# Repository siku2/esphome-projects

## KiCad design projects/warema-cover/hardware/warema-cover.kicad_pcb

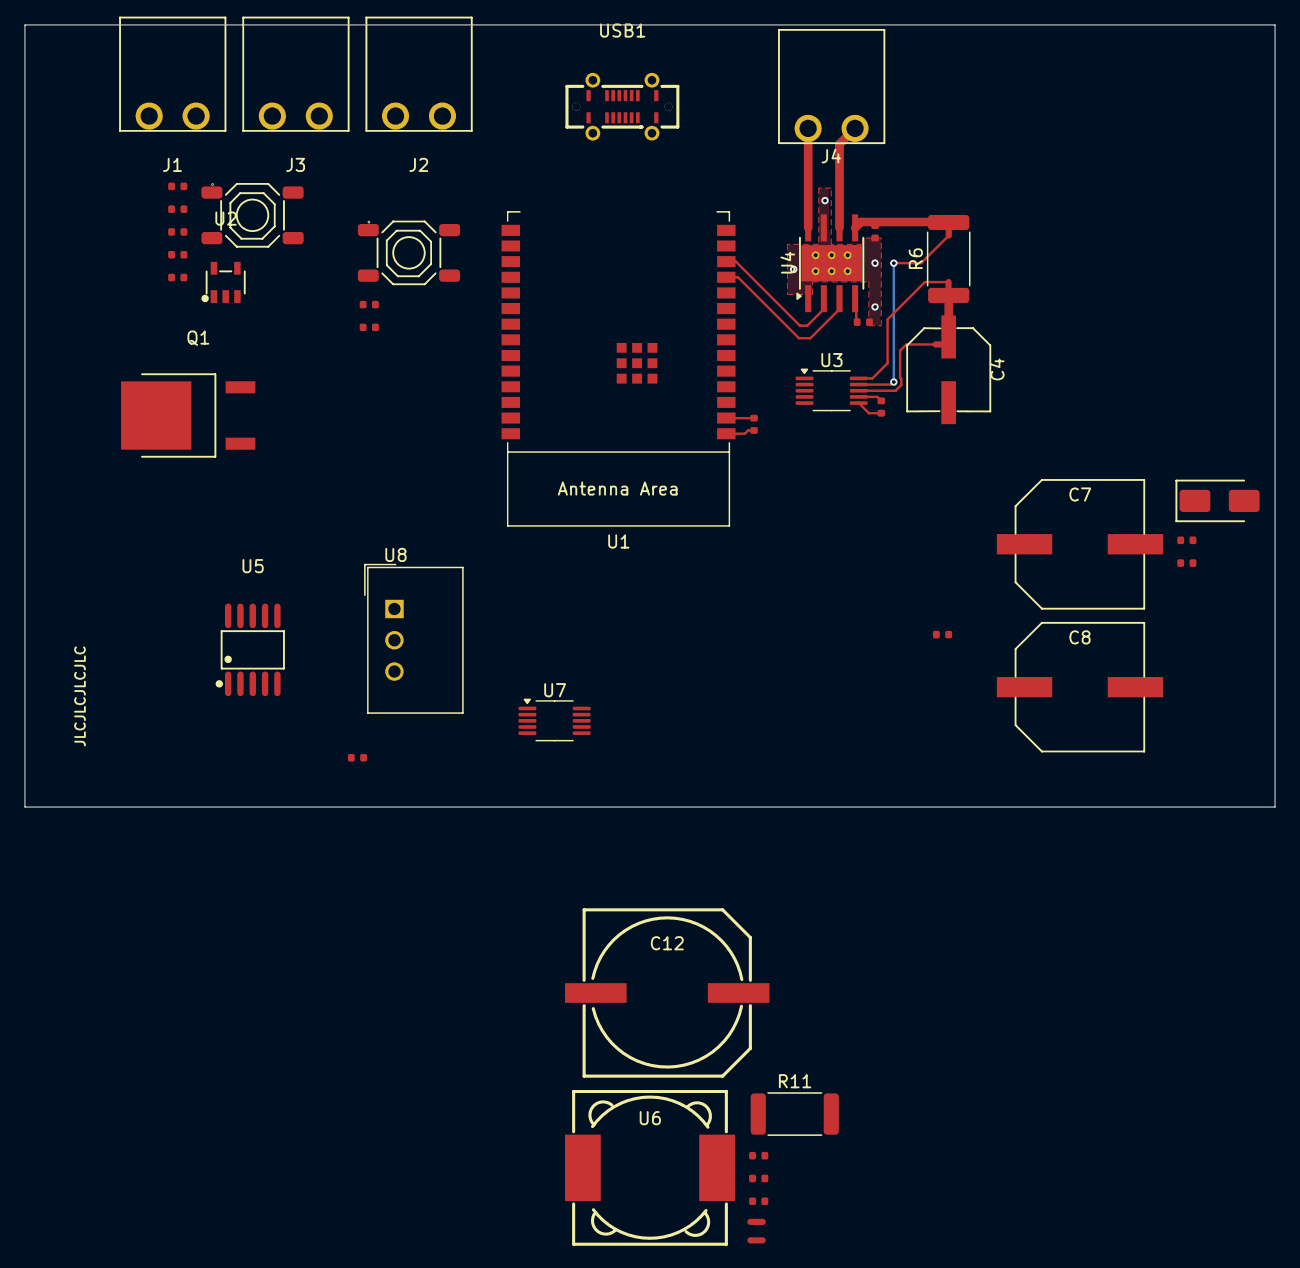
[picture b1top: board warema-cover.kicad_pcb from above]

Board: 2 copper layers, 101.5 x 63.5 mm, 47 parts (0 on the bottom side), 33 nets.

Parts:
C1, C2, C3, C5, C6, C9, C11, C13: 100nF; C_0402
C4: 47uF; CAP-SMD_BD6.3-L6.6-W6.6-LS7.6-FD
C7, C8: 470uF; CAP-SMD_BD10.0-L10.3-W10.3-LS11.0-FD
C10: 220nF; C_0402
C12: 1000uF; CAP-SMD_BD12.5-L13.0-W13.0-RD
D1: SS54; D_SMA
J1: Power Supply; CONN-TH_2P-P3.81_MAX_MX15EDGR-3.81-GN01-02P-CU-A
J2: Solar Panel; CONN-TH_2P-P3.81_MAX_MX15EDGR-3.81-GN01-02P-CU-A
J3: Battery; CONN-TH_2P-P3.81_MAX_MX15EDGR-3.81-GN01-02P-CU-A
J4: Motor; CONN-TH_2P-P3.81_MAX_MX15EDGR-3.81-GN01-02P-CU-A
NT1, NT2, NT3, NT4, NT5: NetTie_2; NetTie-2_SMD_Pad0.5mm
PN1: Part_Num_JLCPCB
Q1: AOD4185_C879147; TO-252-2_L6.6-W6.1-P4.58-LS9.9-BR
R1, R2, R4: 100kΩ; R_0402
R3, R5: 5.1kΩ; R_0402
R6: 15mΩ; R_2512_6332Metric
R7: 24kΩ; R_0402
R8: 120Ω; R_0402
R9: 220kΩ; R_0402
R10: 15kΩ; R_0402
R11: 30mΩ; R_2512_6332Metric
S1, S2: Tactile Button, 160gf; SW-SMD_4P-L5.1-W5.1-P3.70-LS6.5-TL-2
U1: ESP32-C6-WROOM-1
U2: RT9080-33GJ5; TSOT-23-5_L2.9-W1.6-P0.95-LS2.8-BL
U3, U7: INA228; VSSOP-10_3x3mm_P0.5mm
U4: DRV8871DDA; Texas_HTSOP-8-1EP_3.9x4.9mm_P1.27mm_EP2.95x4.9mm_Mask2.4x3.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
U5: CN3767; SSOP-10_L4.9-W3.9-P1.00-LS6.0-BL
U6: CYH125-47UH; IND-SMD_L12.3-W12.3
U8: TSR1-2433E; Converter_DCDC_TRACO_TSR1-xxxxE_THT
USB1: GT-USB-7055BB; USB-C-TH_GT-USB-7055BB

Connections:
+3.3V: C3.2, C5.1, C13.1, R1.1, R2.2, U1.2 (3V3), U2.5 (VOUT), U3.6 (VS), U7.2 (A0), U7.6 (VS), U8.3 (Vout)
+12V: C4.1, C11.2, C12.1, J3.1, NT1.1, NT2.1, NT5.1, R6.1, R11.2, U8.1 (Vin)
/MCU/BOOT: C2.1, S2.3 (C), U1.15 (GPIO9)
/MCU/D+: U1.14 (GPIO13/USB_D+), USB1.A6 (D+), USB1.B6 (D+)
/MCU/D-: U1.13 (GPIO12/USB_D-), USB1.A7 (D-), USB1.B7 (D-)
/MCU/EN: C1.1, R1.2, S1.3 (C), U1.3 (EN/CHIP_PU)
/MCU/I2C_SCL: U1.5 (MTDI/GPIO5/ADC1_CH5), U3.5 (SCL), U7.5 (SCL)
/MCU/I2C_SDA: U1.6 (MTCK/GPIO6/ADC1_CH6), U3.4 (SDA), U7.4 (SDA)
/MCU/MOTOR_IN1: U1.11 (GPIO10), U4.3 (IN1)
/MCU/MOTOR_IN2: U1.12 (GPIO11), U4.2 (IN2)
/MCU/V_{USB}: R4.2, U2.1 (VIN), USB1.A4 (VBUS), USB1.A9 (VBUS), USB1.B4 (VBUS), USB1.B9 (VBUS)
/Motor Control/OUT1: J4.1, U4.6 (OUT1)
/Motor Control/OUT2: J4.2, U4.8 (OUT2)
/Motor Control/VM: C6.2, NT3.1, R6.2, U4.5 (VM)
/Power/BAT: NT5.2, U5.7 (BAT), U7.9 (Vin-)
/Power/CSP: NT4.1, U5.8 (CSP), U7.8 (Vbus), U7.10 (Vin+)
/Power/VCC: C7.1, C8.1, C9.1, Q1.3 (S), R9.1, U5.9 (VCC)
GND: C1.2, C2.2, C3.1, C4.2, C5.2, C6.1, C7.2, C8.2, C10.2, C11.1, C12.2, C13.2, D1.2, J1.2, J2.2, J3.2, R3.1, R5.2, R7.2, R10.1, S1.1 (A), S2.1 (A), U1.1 (GND), U1.28 (GND), U1.29 (GND), U2.2 (GND), U3.1 (A1), U3.2 (A0), U3.7 (GND), U4.1 (GND), U4.7 (GND), U4.9 (GND), U5.2 (GND), U7.1 (A1), U7.7 (GND), U8.2 (GND), USB1.A1 (GND), USB1.A12 (GND), USB1.B1 (GND), USB1.B12 (GND)
unnamed: C10.1, R8.2
unnamed: NT4.2, R11.1, U6.2
unnamed: D1.1, Q1.2 (D), U6.1
unnamed: Q1.1 (G), U5.10 (DRV)
unnamed: R2.1, U1.10 (GPIO8)
unnamed: R4.1, U2.3 (EN)
unnamed: NT1.2, U3.8 (Vbus)
unnamed: NT2.2, U3.10 (Vin+)
unnamed: NT3.2, U3.9 (Vin-)
unnamed: R7.1, U4.4 (ILIM)
unnamed: R8.1, U5.5 (COM)
unnamed: R9.2, R10.2, U5.6 (MPPT)
unnamed: C9.2, U5.1 (VG)
unnamed: R3.2, USB1.A5 (CC1)
unnamed: R5.1, USB1.B5 (CC2)

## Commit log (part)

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2025-10-05 feat(m5stack_4encodermotor): add cover component for M5Stack 4 Encoder Motor with configuration options
2025-10-05 refactor(m5stack_4encodermotor): remove obsolete YAML configuration for M5Stack 4 Encoder Motor
2025-10-05 feat(m5stack_cores3_lite): enhance YAML configuration with detailed component descriptions and internal binary sensors
2025-10-05 fix(m5stack_cores3_lite): update external component source to GitHub repository for AW9523
2025-10-05 feat(m5stack_4encodermotor): add debug logging for motor mode, speed, and soft start/stop settings
2025-10-05 fix(m5stack_4encodermotor): correct REG_SOFT_START_STOP definition to match hardware specification
2025-10-06 fix(m5stack_4encodermotor): update motor register definitions and enhance config logging for motor status
2025-10-06 refactor(m5stack_4encodermotor): rename motor speed functions to reflect PWM duty usage
2025-10-06 fix(m5stack_4encodermotor): set default value of positive_is_up to True in CONFIG_SCHEMA
2025-10-06 fix(m5stack_cores3_lite): correct syntax for output ID in YAML configuration
2025-10-06 refactor(elechouse_cc1101): add vendored version of the driver
2025-10-06 refactor(elechouse_cc1101, somfy_cover): update CONFIG_SCHEMA to use cv.All for enhanced validation
2025-10-06 refactor(somfy_cover): update CONFIG_SCHEMA to use cover.cover_schema for improved clarity
2025-10-07 refactor(devcontainer): remove Dockerfile and update features for improved configuration
2025-10-07 refactor: CC1101 driver integration in Somfy cover component
    - Removed the obsolete ELECHOUSE_CC1101 driver header file.
    - Updated the Somfy cover component to use new methods for enabling TX and IDLE states in the CC1101 driver.
2025-10-07 refactor: rename cc1101 component
2025-10-07 refactor(cc1101): update pin handling and logging for improved clarity
2025-10-07 refactor(somfy_cover): simplify configuration schema and enhance command handling
2025-10-07 refactor(cc1101, somfy_cover): enhance logging and restructure reset functionality
2025-10-07 refactor(cc1101): update documentation and enhance logging for part number and version
2025-10-08 refactor(cc1101): initialize TX pin state before reset
2025-10-08 refactor(somfy_cover): fix rolling code and remote address handling in frame construction
2025-10-08 feat: adopt esphome clang config
2025-10-08 refactor: use pyproject for local esphome access
2025-10-08 feat(cc1101): add MISO pin support and enhance reset handling
2025-10-08 refactor(cc1101): rename frequency handling functions for clarity
2025-10-08 feat(cc1101): log MISO pin configuration in dump_config
2025-10-08 fix(cc1101): improve frequency logging precision in dump_config and related methods
2025-10-08 feat(cc1101): add debug logging for TX and IDLE state transitions
2025-10-08 fix(somfy_cover): replace delay_microseconds_safe with delayMicroseconds for consistency
2025-10-08 feat(cc1101): add always listen functionality and corresponding methods
2025-10-08 feat(cc1101): enhance dump_config to log channel, CC mode, and always listen status
2025-10-08 feat(cc1101): enable RX mode if always listen is active during setup
2025-10-08 feat(cc1101): update pin configurations to use internal GPIO for TX and RX
2025-10-08 feat(somfy_cover): refactor send_frame_ to utilize emit_pulse for better clarity
2025-10-08 fix(cc1101): correct emitter pin usage in emit_pulse and update pin handling methods
2025-10-08 feat(somfy_cover): log frame before obfuscation
2025-10-08 feat(somfy_cover): add reset rolling code functionality and corresponding action
2025-10-08 refactor(somfy_cover): improve frame building and sending logic for clarity and consistency
2025-10-08 fix(cc1101): change read_reg_ to use READ_SINGLE instead of READ_BURST for correct register reading
2025-10-08 refactor(cc1101): remove useless configs and add useful ones
2025-10-08 feat(cc1101): add version check during setup and log additional configuration details
2025-10-08 feat(cc1101): add part number retrieval and logging during setup and configuration dump
2025-10-08 refactor(cc1101): remove unused logging of M2 parameters in config dump
2025-10-08 fix(somfy_cover): update get_tx_pin to return pointer for digital_write call
2025-10-08 fix(uv.lock): update esphome-projects version from 0.1.0 to 0.0.0
2025-11-17 chore(deps): update actions/checkout action to v5
2026-03-13 chore(deps): lock file maintenance
2026-04-06 feat: add esphome base config
2026-04-06 chore: change default language to en
2026-04-06 refactor: add translations to cp579epd
2026-04-06 feat: add grill-display
2026-04-06 fix: double vars
2026-04-06 fix: no need to pass down substitutions
2026-04-06 feat: add grill_thermal_model
2026-04-06 feat: add the grill ui
2026-04-06 chore: remove required value placeholders
2026-04-06 fix: source component from git
2026-04-06 fix: external component path
2026-04-06 fix: update epd periodically
2026-04-06 feat: improve the cooking page
2026-04-06 fix: remove other strings from time sensors
2026-04-07 feat: simplify the ui som emore
2026-04-08 chore(deps): update actions/checkout digest to 34e1148
2026-04-08 chore(deps): update astral-sh/setup-uv digest to d0cc045
2026-04-08 chore(deps): update awalsh128/cache-apt-pkgs-action digest to 2c09a5e
2026-04-08 chore(deps): update actions/checkout action to v6
2026-04-08 chore(deps): update actions/deploy-pages action to v5
2026-04-08 chore(deps): update actions/upload-pages-artifact action to v4
2026-04-13 chore(deps): update actions/upload-pages-artifact action to v5
2026-04-16 chore(deps): update astral-sh/setup-uv action to v7
2026-04-21 chore(deps): update astral-sh/setup-uv action to v8
2026-05-02 chore: dc lock file
2026-05-02 refactor: spring cleaning
2026-05-02 chore: remove mac suffix
2026-05-02 feat: add initial catimor project
2026-05-02 fix(grill-display): update analog clock widget
2026-05-02 refactor: update translation system for new substitutions
2026-05-02 fix(grill-display): lvgl v9 compatibility
2026-05-02 chore(catimor): change default display timeout to 10s
2026-05-02 fix(m5s3l): set lcd backlight restore mode to always on
2026-05-02 feat(catimor): add blinds control page
2026-05-02 feat(catimor): add home page
2026-05-03 fix(catimor): only sync position when blinds aren't moving
2026-05-07 feat(catimor): add climate control page
2026-05-09 refactor: update cp579epd to use new localization
2026-05-10 feat: add esp32_s3_cam package
2026-05-13 feat: create tflite custom component
2026-05-13 chore: add jupyter to devcontainer
2026-05-13 feat: create aquasense project
2026-05-13 fix(aquasense): camera does not need !extend
2026-05-13 fix(aquasense): stick to jpeg while testing
2026-05-27 chore: update esphome to 2026.5.1
2026-05-27 style: format with ruff
2026-05-27 docs(e32s3cam): document flash peripheral
2026-05-27 chore: update devcontainer
2026-05-27 feat: add camera snapshot component
2026-05-27 feat(tflite): add support for external models
2026-05-27 feat(camera_snapshot): add listener support
2026-05-27 feat(aquasense): add model and first digit sensor
2026-05-27 feat(aquasense): make crop region an input
2026-05-27 feat(camera_snapshot): support rotating
2026-05-27 fix(tflite): use is_failed instead of failed
2026-05-27 feat(aquasense): add remaining digits and combine
2026-05-27 feat(tflite): support defining rects through width and height
2026-05-27 refactor(aquasense): add sensor names
2026-05-27 chore(deps): update ghcr.io/devcontainers/features/docker-outside-of-docker docker tag to v1.10.0
2026-05-28 feat(aquasense): add full reading
2026-05-28 feat(tflite): support analog_continuous_cw output format
2026-05-28 fix(tflite): run inference in on_snapshot callback
    Multiple sensors might share the same interpreter and end up overwriting
    each other.
2026-05-28 fix(camera_snapshot): invalidate cache after jpeg decode
2026-05-28 fix(camera_snapshot): add prime phase and notify incrementally
    The prime phase serves to discard buffered camera frames before taking a
    snapshot.
    Notifying one listener per loop iteration is to avoid blocking the main
    loop.
2026-06-05 feat(aquasense): add flash config and improve calc
2026-06-05 feat(camera_snapshot): explicitly drain frame buffer after pre_snapshot
2026-06-05 feat(aquasense): improve total tracking
2026-06-05 feat: add max_update_interval to camera sensor
2026-06-05 feat(tflite): add min_fit parameter and rounding
2026-06-25 refactor(aquasense): add explicit id to ota
2026-06-27 fix(tflite): add explicit unit to max update interval default
2026-06-27 feat(aquasense): split across models
